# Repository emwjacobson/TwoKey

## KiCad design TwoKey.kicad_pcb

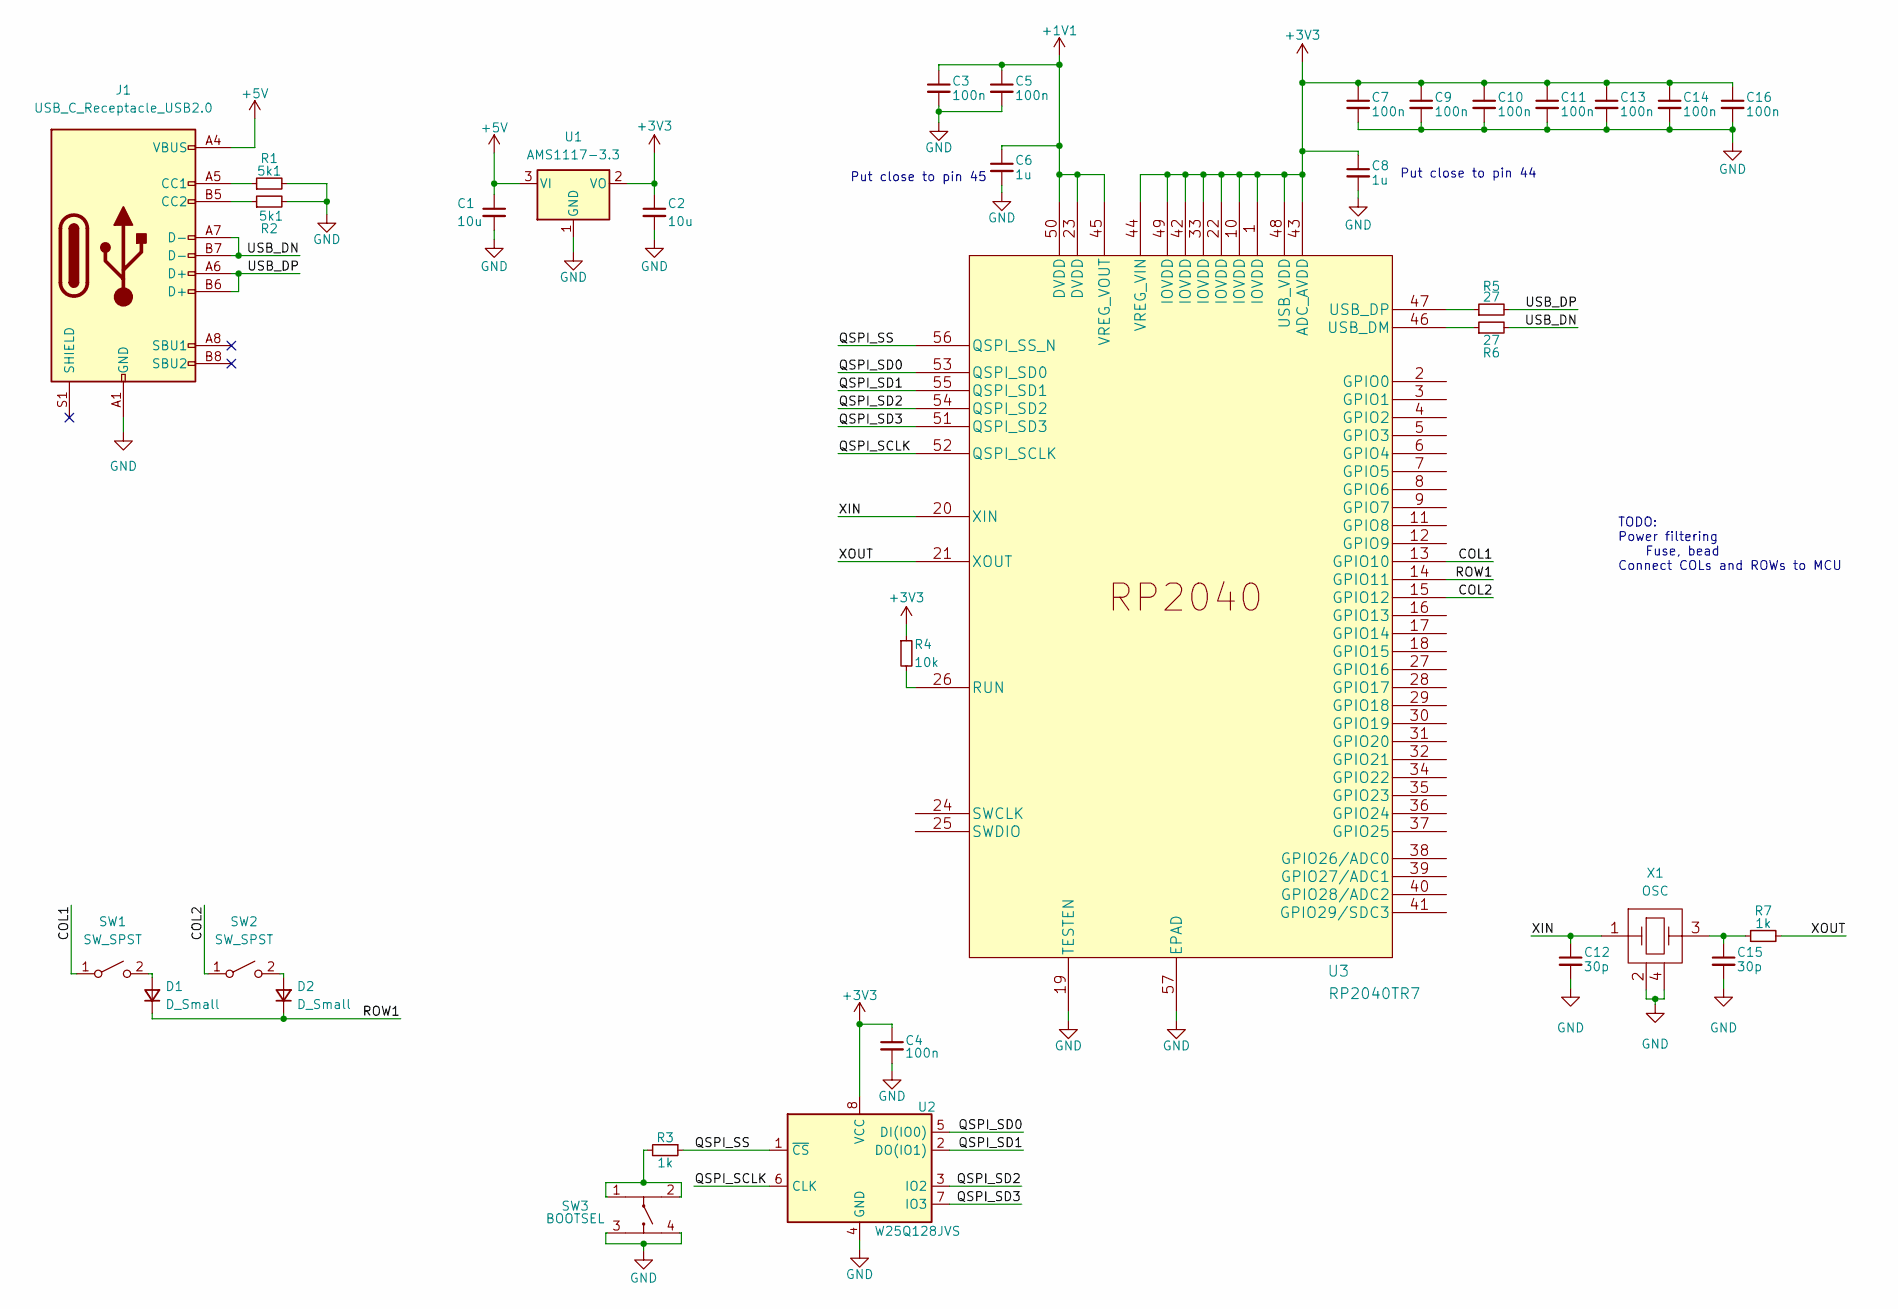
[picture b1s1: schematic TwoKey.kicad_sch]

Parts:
C1, C2: 10u; C_0603_1608Metric; Manufacturer Part Number CL10A106MQ8NNNC; LCSC Part Number C1691
C3, C4, C5, C7, C9, C10, C11, C13, C14, C16: 100n; C_0603_1608Metric; Manufacturer Part Number CL10B104KB8NNNC; LCSC Part Number C1591
C6, C8: 1u; C_0603_1608Metric; Manufacturer Part Number CL10A105KO8NNNC; LCSC Part Number C1592
C12, C15: 30p; C_0603_1608Metric; Manufacturer Part Number CC0603JRNPO9BN300; LCSC Part Number C113797
D1, D2: D_Small; D_SOD-123; Manufacturer Part Number 1N4148W; LCSC Part Number C115103
J1: USB_C_Receptacle_USB2.0; USB_C_Receptacle_HRO_TYPE-C-31-M-12; Manufacturer Part Number KH-TYPE-C-16P; LCSC Part Number C709357
R1, R2: 5k1; R_0603_1608Metric; Manufacturer Part Number 0603WAF5101T5E; LCSC Part Number C23186
R3, R7: 1k; R_0603_1608Metric; Manufacturer Part Number 0603WAF1001T5E; LCSC Part Number C21190
R4: 10k; R_0603_1608Metric; Manufacturer Part Number 0603WAF1002T5E; LCSC Part Number C25804
R5, R6: 27; R_0603_1608Metric; Manufacturer Part Number 0603WAF270JT5E; LCSC Part Number C25190
SW1, SW2: SW_SPST; Kailh_socket_MX
SW3: BOOTSEL; DTSL-61N-V; Manufacturer Part Number DTSL-61N-V-T/R; LCSC Part Number C495902
U1: AMS1117-3.3; SOT-223-3_TabPin2; Manufacturer Part Number AMS1117-3.3V; LCSC Part Number C173386
U2: W25Q128JVS; SOIC-8_5.23x5.23mm_P1.27mm; Manufacturer Part Number W25Q128JVSIQ; LCSC Part Number C113767
U3: RP2040TR7
X1: OSC; Crystal_SMD_3225-4Pin_3.2x2.5mm; Manufacturer Part Number X322512MSB4SI; LCSC Part Number C9002

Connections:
+1V1: C3.1, C5.1, C6.1, U3.23 (DVDD), U3.45 (VREG_VOUT), U3.50 (DVDD)
+3V3: C2.1, C4.1, C7.1, C8.1, C9.1, C10.1, C11.1, C13.1, C14.1, C16.1, R4.1, U1.2 (VO), U2.8 (VCC), U3.1 (IOVDD), U3.10 (IOVDD), U3.22 (IOVDD), U3.33 (IOVDD), U3.42 (IOVDD), U3.43 (ADC_AVDD), U3.44 (VREG_VIN), U3.48 (USB_VDD), U3.49 (IOVDD)
+5V: C1.1, J1.A4 (VBUS), J1.A9 (VBUS), J1.B4 (VBUS), J1.B9 (VBUS), U1.3 (VI)
/COL1: SW1.1 (A), U3.13 (GPIO10)
/COL2: SW2.1 (A), U3.15 (GPIO12)
/QSPI_SCLK: U2.6 (CLK), U3.52 (QSPI_SCLK)
/QSPI_SD0: U2.5 (DI(IO0)), U3.53 (QSPI_SD0)
/QSPI_SD1: U2.2 (DO(IO1)), U3.55 (QSPI_SD1)
/QSPI_SD2: U2.3 (IO2), U3.54 (QSPI_SD2)
/QSPI_SD3: U2.7 (IO3), U3.51 (QSPI_SD3)
/QSPI_SS: R3.1, U2.1 (~CS), U3.56 (QSPI_SS_N)
/ROW1: D1.1 (K), D2.1 (K), U3.14 (GPIO11)
/USB_DN: J1.A7 (D-), J1.B7 (D-), R6.2
/USB_DP: J1.A6 (D+), J1.B6 (D+), R5.2
/XIN: C12.1, U3.20 (XIN), X1.1
/XOUT: R7.2, U3.21 (XOUT)
GND: C1.2, C2.2, C3.2, C4.2, C5.2, C6.2, C7.2, C8.2, C9.2, C10.2, C11.2, C12.2, C13.2, C14.2, C15.2, C16.2, J1.A1 (GND), J1.A12 (GND), J1.B1 (GND), J1.B12 (GND), R1.2, R2.2, SW3.3, SW3.4, U1.1 (GND), U2.4 (GND), U3.19 (TESTEN), U3.57 (EPAD), X1.2, X1.4
unnamed: C15.1, R7.1, X1.3
unnamed: D1.2 (A), SW1.2 (B)
unnamed: D2.2 (A), SW2.2 (B)
unnamed: J1.A5 (CC1), R1.1
unnamed: J1.B5 (CC2), R2.1
unnamed: R3.2, SW3.1, SW3.2
unnamed: R4.2, U3.26 (RUN)
unnamed: R5.1, U3.47 (USB_DP)
unnamed: R6.1, U3.46 (USB_DM)

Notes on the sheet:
Put close to pin 45
TODO: Power filtering Fuse, bead Connect COLs and ROWs to MCU
Put close to pin 44

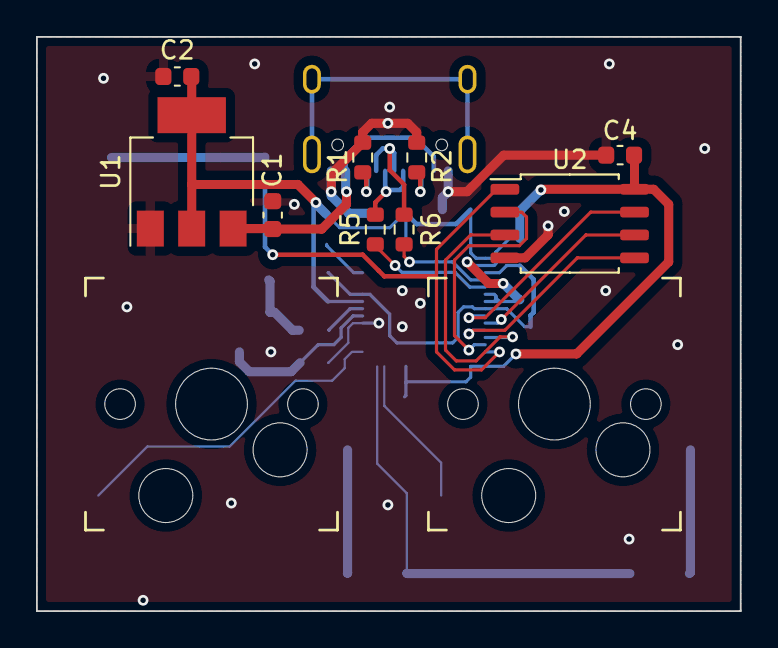
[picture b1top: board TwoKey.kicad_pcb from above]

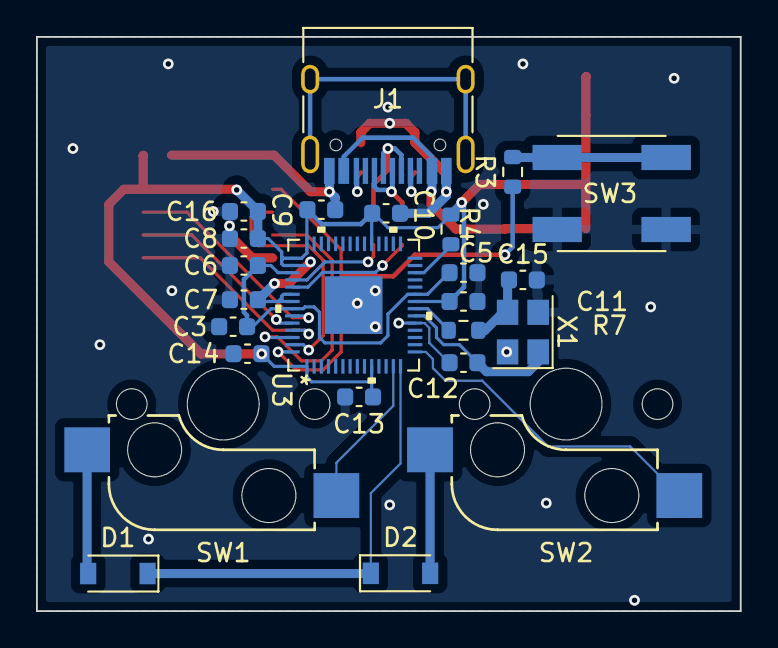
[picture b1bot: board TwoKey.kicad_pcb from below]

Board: 2 copper layers, 39.1 x 31.9 mm, 33 parts (22 on the bottom side), 26 nets.

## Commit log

2022-04-23 Initial commit of TwoKey board
2022-04-23 Started work on condencing items
2022-04-24 Reworked some placement and added submodule
2022-04-24 Condenced items into initial pcb
2022-04-24 Readjusted more componenets (DRC not passing)
2022-04-27 Finished routing of all traces
2022-04-27 Finished routing some traces
